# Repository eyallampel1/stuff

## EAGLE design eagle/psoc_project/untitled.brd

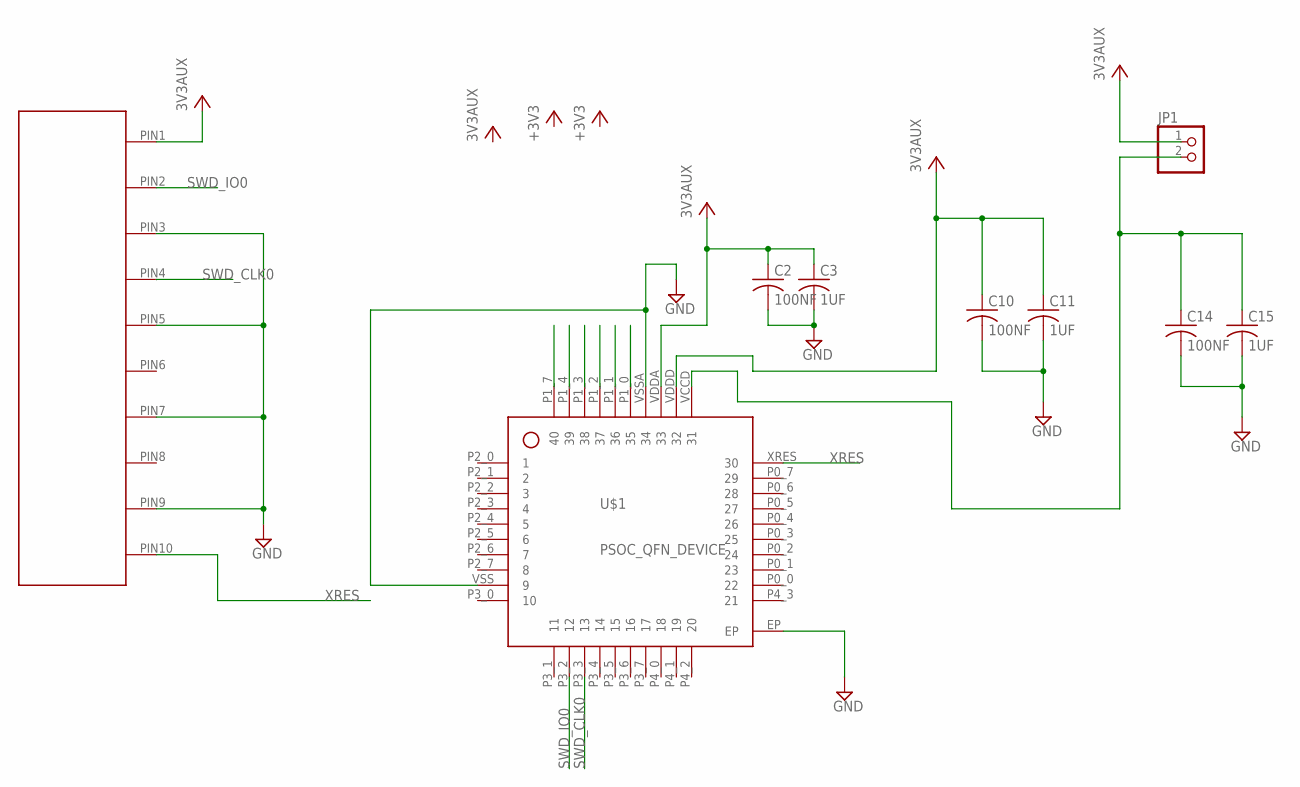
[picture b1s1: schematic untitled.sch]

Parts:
C2, C10, C14: 100NF; C0603
C3, C11, C15: 1UF; C0603
JP1: PINHD-1X2/90; 1X02/90
U$1: PSOC_QFN_DEVICE; PSOC_QFN_PACKEGE
U$2: PSOC_10_PIN_HEADER_DEVICE; PSOC_10_PIN_HEADER

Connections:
GND: C2.2, C3.2, C10.2, C11.2, C14.2, C15.2, U$1.EP, U$1.VSS (9), U$1.VSSA (34), U$2.PIN3 (GND), U$2.PIN5 (GND), U$2.PIN7 (GND), U$2.PIN9 (GND)
SWD_CLK0: U$1.P3_3 (13), U$2.PIN4 (SWD_CLK0)
SWD_IO0: U$1.P3_2 (12), U$2.PIN2 (SWD_IO0)
VCC: C2.1, C3.1, C10.1, C11.1, JP1.1, U$1.VDDA (33), U$1.VDDD (32), U$2.PIN1 (3V3_AUX)
VCC2: C14.1, C15.1, JP1.2, U$1.VCCD (31)
XRES: U$1.XRES (30), U$2.PIN10 (XRES)

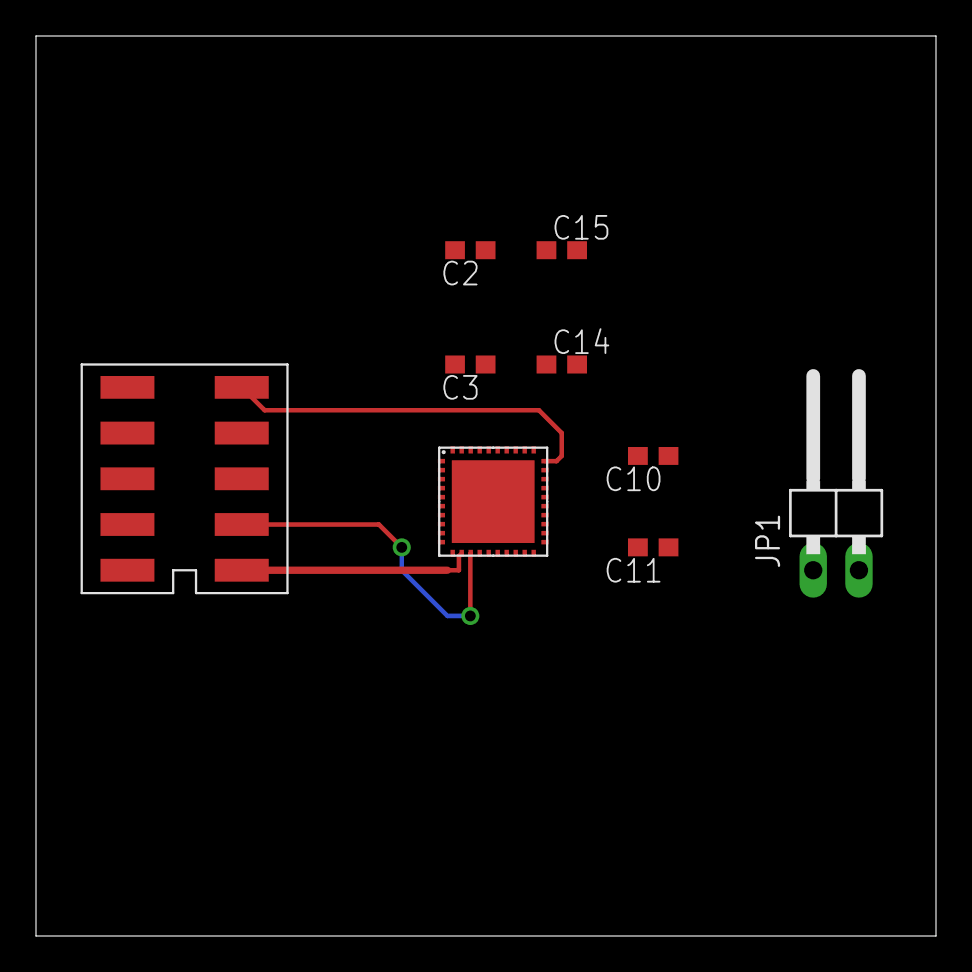
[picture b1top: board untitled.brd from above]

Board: 2 copper layers, 50.0 x 50.0 mm, 9 parts (0 on the bottom side), 6 nets.

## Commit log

2016-02-18 team view
2016-03-01 uploadd com printer
2016-03-01 send serial commands
2016-04-16 Create hdl_books
2016-04-16 Create hdl_books
    vhdl books
2016-04-16 Create dummy
2016-05-07 eeprom at work - to work
2016-05-09 added uart support
2016-05-17 my whole knowledge !!!
2016-05-18 ver2
2016-05-21 3d model pcb
2016-05-22 tyco 3d model
2016-05-25 eagle pcb
2016-06-10 initial
2016-06-10 initial project upload
2016-06-21 first
2016-06-21 initial upload
2016-06-23 start
2016-08-31 inital
